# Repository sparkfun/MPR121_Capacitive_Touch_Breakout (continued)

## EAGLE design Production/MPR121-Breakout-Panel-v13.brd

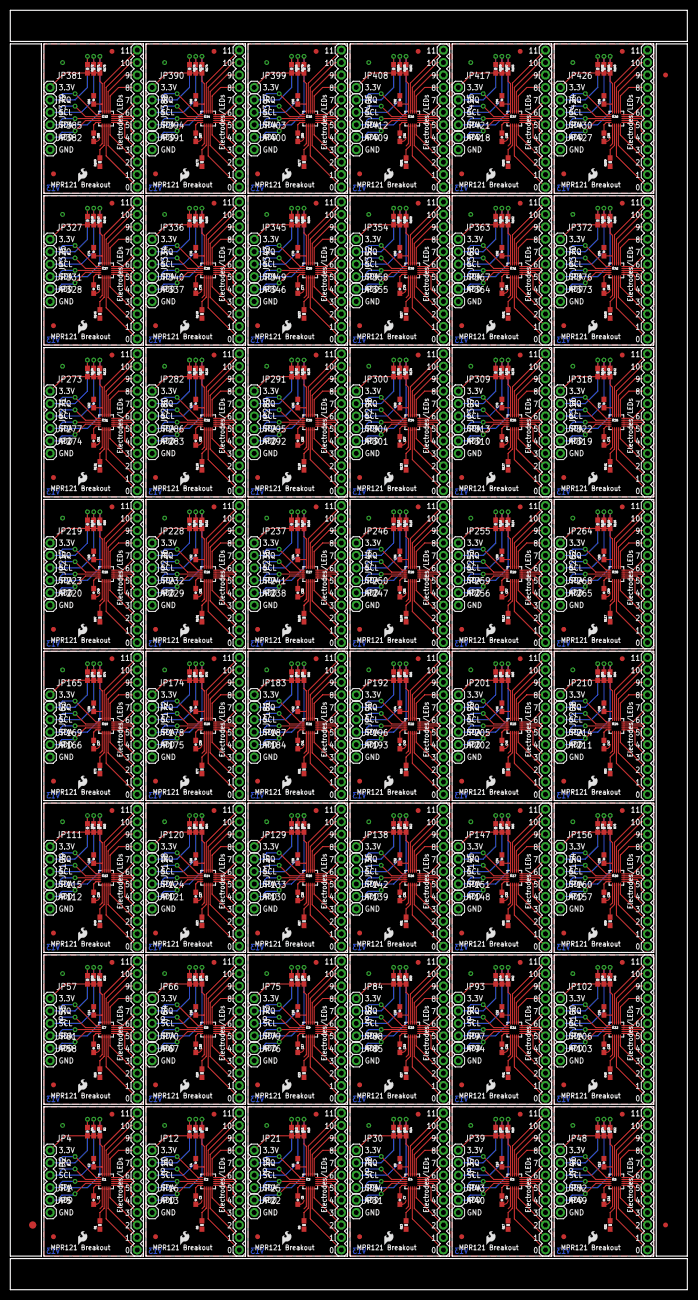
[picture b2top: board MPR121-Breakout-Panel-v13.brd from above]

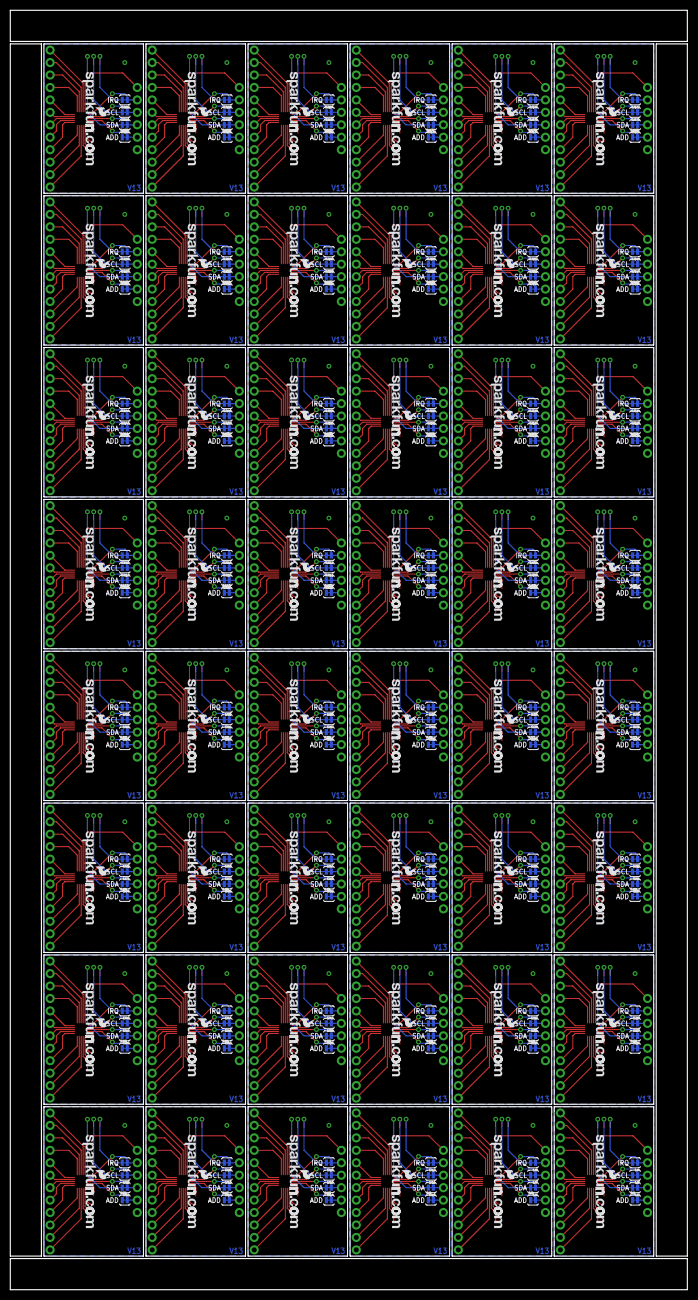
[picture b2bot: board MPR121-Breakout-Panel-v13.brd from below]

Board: 2 copper layers, 138.2 x 261.1 mm, 963 parts (240 on the bottom side), 1104 nets.

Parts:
C1, C2, C3, C4, C5, C6, C7, C8, C9, C10, C11, C12, C13, C14, C15, C16, C17, C18, C19, C20, C21, C22, C23, C24, C25, C26, C27, C28, C29, C30, C31, C32, C33, C34, C35, C36, C37, C38, C39, C40, C41, C42, C43, C44, C45, C46, C47, C48, C49, C50, C51, C52, C53, C54, C55, C56, C57, C58, C59, C60, C61, C62, C63, C64, C65, C66, C67, C68, C69, C70, C71, C72, C73, C74, C75, C76, C77, C78, C79, C80, C81, C82, C83, C84, C85, C86, C87, C88, C89, C90, C91, C92, C93, C94, C95, C96: 0.1uF; 0603-CAP
E$1: FIDUCIAL-1.5X3
E$4, E$5: FIDUCIAL-1X2
IC1, IC2, IC3, IC4, IC5, IC6, IC7, IC8, IC9, IC10, IC11, IC12, IC13, IC14, IC15, IC16, IC17, IC18, IC19, IC20, IC21, IC22, IC23, IC24, IC25, IC26, IC27, IC28, IC29, IC30, IC31, IC32, IC33, IC34, IC35, IC36, IC37, IC38, IC39, IC40, IC41, IC42, IC43, IC44, IC45, IC46, IC47, IC48: MPR121; QFN-20-0.4MM-V2
JP1, JP16, JP25, JP34, JP43, JP52, JP61, JP70, JP79, JP88, JP97, JP106, JP115, JP124, JP133, JP142, JP151, JP160, JP169, JP178, JP187, JP196, JP205, JP214, JP223, JP232, JP241, JP250, JP259, JP268, JP277, JP286, JP295, JP304, JP313, JP322, JP331, JP340, JP349, JP358, JP367, JP376, JP385, JP394, JP403, JP412, JP421, JP430: ADDR; 1X01
JP2, JP10, JP19, JP28, JP37, JP46, JP55, JP64, JP73, JP82, JP91, JP100, JP109, JP118, JP127, JP136, JP145, JP154, JP163, JP172, JP181, JP190, JP199, JP208, JP217, JP226, JP235, JP244, JP253, JP262, JP271, JP280, JP289, JP298, JP307, JP316, JP325, JP334, JP343, JP352, JP361, JP370, JP379, JP388, JP397, JP406, JP415, JP424: I2C; 1X03
JP3, JP11, JP20, JP29, JP38, JP47, JP56, JP65, JP74, JP83, JP92, JP101, JP110, JP119, JP128, JP137, JP146, JP155, JP164, JP173, JP182, JP191, JP200, JP209, JP218, JP227, JP236, JP245, JP254, JP263, JP272, JP281, JP290, JP299, JP308, JP317, JP326, JP335, JP344, JP353, JP362, JP371, JP380, JP389, JP398, JP407, JP416, JP425: Electrodes; 1X12
JP4, JP12, JP21, JP30, JP39, JP48, JP57, JP66, JP75, JP84, JP93, JP102, JP111, JP120, JP129, JP138, JP147, JP156, JP165, JP174, JP183, JP192, JP201, JP210, JP219, JP228, JP237, JP246, JP255, JP264, JP273, JP282, JP291, JP300, JP309, JP318, JP327, JP336, JP345, JP354, JP363, JP372, JP381, JP390, JP399, JP408, JP417, JP426: 3.3V; 1X01
JP5, JP13, JP22, JP31, JP40, JP49, JP58, JP67, JP76, JP85, JP94, JP103, JP112, JP121, JP130, JP139, JP148, JP157, JP166, JP175, JP184, JP193, JP202, JP211, JP220, JP229, JP238, JP247, JP256, JP265, JP274, JP283, JP292, JP301, JP310, JP319, JP328, JP337, JP346, JP355, JP364, JP373, JP382, JP391, JP400, JP409, JP418, JP427: GND; 1X01
JP6, JP14, JP23, JP32, JP41, JP50, JP59, JP68, JP77, JP86, JP95, JP104, JP113, JP122, JP131, JP140, JP149, JP158, JP167, JP176, JP185, JP194, JP203, JP212, JP221, JP230, JP239, JP248, JP257, JP266, JP275, JP284, JP293, JP302, JP311, JP320, JP329, JP338, JP347, JP356, JP365, JP374, JP383, JP392, JP401, JP410, JP419, JP428: LOGO-SFESK; SFE-LOGO-FLAME
JP7, JP15, JP24, JP33, JP42, JP51, JP60, JP69, JP78, JP87, JP96, JP105, JP114, JP123, JP132, JP141, JP150, JP159, JP168, JP177, JP186, JP195, JP204, JP213, JP222, JP231, JP240, JP249, JP258, JP267, JP276, JP285, JP294, JP303, JP312, JP321, JP330, JP339, JP348, JP357, JP366, JP375, JP384, JP393, JP402, JP411, JP420, JP429: LOGO-SFENEW; SFE-NEW-WEBLOGO
JP8, JP9, JP17, JP18, JP26, JP27, JP35, JP36, JP44, JP45, JP53, JP54, JP62, JP63, JP71, JP72, JP80, JP81, JP89, JP90, JP98, JP99, JP107, JP108, JP116, JP117, JP125, JP126, JP134, JP135, JP143, JP144, JP152, JP153, JP161, JP162, JP170, JP171, JP179, JP180, JP188, JP189, JP197, JP198, JP206, JP207, JP215, JP216, JP224, JP225, JP233, JP234, JP242, JP243, JP251, JP252, JP260, JP261, JP269, JP270, JP278, JP279, JP287, JP288, JP296, JP297, JP305, JP306, JP314, JP315, JP323, JP324, JP332, JP333, JP341, JP342, JP350, JP351, JP359, JP360, JP368, JP369, JP377, JP378, JP386, JP387, JP395, JP396, JP404, JP405, JP413, JP414, JP422, JP423, JP431, JP432: FIDUCIAL1X2; FIDUCIAL-1X2
R1, R5, R9, R13, R17, R21, R25, R29, R33, R37, R41, R45, R49, R53, R57, R61, R65, R69, R73, R77, R81, R85, R89, R93, R97, R101, R105, R109, R113, R117, R121, R125, R129, R133, R137, R141, R145, R149, R153, R157, R161, R165, R169, R173, R177, R181, R185, R189: 75k; 0603-RES
R2, R3, R4, R6, R7, R8, R10, R11, R12, R14, R15, R16, R18, R19, R20, R22, R23, R24, R26, R27, R28, R30, R31, R32, R34, R35, R36, R38, R39, R40, R42, R43, R44, R46, R47, R48, R50, R51, R52, R54, R55, R56, R58, R59, R60, R62, R63, R64, R66, R67, R68, R70, R71, R72, R74, R75, R76, R78, R79, R80, R82, R83, R84, R86, R87, R88, R90, R91, R92, R94, R95, R96, R98, R99, R100, R102, R103, R104, R106, R107, R108, R110, R111, R112, R114, R115, R116, R118, R119, R120, R122, R123, R124, R126, R127, R128, R130, R131, R132, R134, R135, R136, R138, R139, R140, R142, R143, R144, R146, R147, R148, R150, R151, R152, R154, R155, R156, R158, R159, R160, R162, R163, R164, R166, R167, R168, R170, R171, R172, R174, R175, R176, R178, R179, R180, R182, R183, R184, R186, R187, R188, R190, R191, R192: 10k; 0603-RES
SJ1, SJ2, SJ3, SJ4, SJ5, SJ6, SJ7, SJ8, SJ9, SJ10, SJ11, SJ12, SJ13, SJ14, SJ15, SJ16, SJ17, SJ18, SJ19, SJ20, SJ21, SJ22, SJ23, SJ24, SJ25, SJ26, SJ27, SJ28, SJ29, SJ30, SJ31, SJ32, SJ33, SJ34, SJ35, SJ36, SJ37, SJ38, SJ39, SJ40, SJ41, SJ42, SJ43, SJ44, SJ45, SJ46, SJ47, SJ48, SJ49, SJ50, SJ51, SJ52, SJ53, SJ54, SJ55, SJ56, SJ57, SJ58, SJ59, SJ60, SJ61, SJ62, SJ63, SJ64, SJ65, SJ66, SJ67, SJ68, SJ69, SJ70, SJ71, SJ72, SJ73, SJ74, SJ75, SJ76, SJ77, SJ78, SJ79, SJ80, SJ81, SJ82, SJ83, SJ84, SJ85, SJ86, SJ87, SJ88, SJ89, SJ90, SJ91, SJ92, SJ93, SJ94, SJ95, SJ96, SJ97, SJ98, SJ99, SJ100, SJ101, SJ102, SJ103, SJ104, SJ105, SJ106, SJ107, SJ108, SJ109, SJ110, SJ111, SJ112, SJ113, SJ114, SJ115, SJ116, SJ117, SJ118, SJ119, SJ120, SJ121, SJ122, SJ123, SJ124, SJ125, SJ126, SJ127, SJ128, SJ129, SJ130, SJ131, SJ132, SJ133, SJ134, SJ135, SJ136, SJ137, SJ138, SJ139, SJ140, SJ141, SJ142, SJ143, SJ144, SJ145, SJ146, SJ147, SJ148, SJ149, SJ150, SJ151, SJ152, SJ153, SJ154, SJ155, SJ156, SJ157, SJ158, SJ159, SJ160, SJ161, SJ162, SJ163, SJ164, SJ165, SJ166, SJ167, SJ168, SJ169, SJ170, SJ171, SJ172, SJ173, SJ174, SJ175, SJ176, SJ177, SJ178, SJ179, SJ180, SJ181, SJ182, SJ183, SJ184, SJ185, SJ186, SJ187, SJ188, SJ189, SJ190, SJ191, SJ192: SOLDERJUMPERTRACE; SJ_2S-TRACE

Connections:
3.3V: C2.1, IC1.20, JP4.1, R2.2, R3.2, R4.2
3.3V1: C4.1, IC2.20, JP12.1, R6.2, R7.2, R8.2
3.3V2: C6.1, IC3.20, JP21.1, R10.2, R11.2, R12.2
3.3V3: C8.1, IC4.20, JP30.1, R14.2, R15.2, R16.2
3.3V4: C10.1, IC5.20, JP39.1, R18.2, R19.2, R20.2
3.3V5: C12.1, IC6.20, JP48.1, R22.2, R23.2, R24.2
3.3V6: C14.1, IC7.20, JP57.1, R26.2, R27.2, R28.2
3.3V7: C16.1, IC8.20, JP66.1, R30.2, R31.2, R32.2
3.3V8: C18.1, IC9.20, JP75.1, R34.2, R35.2, R36.2
3.3V9: C20.1, IC10.20, JP84.1, R38.2, R39.2, R40.2
3.3V10: C22.1, IC11.20, JP93.1, R42.2, R43.2, R44.2
3.3V11: C24.1, IC12.20, JP102.1, R46.2, R47.2, R48.2
3.3V12: C26.1, IC13.20, JP111.1, R50.2, R51.2, R52.2
3.3V13: C28.1, IC14.20, JP120.1, R54.2, R55.2, R56.2
3.3V14: C30.1, IC15.20, JP129.1, R58.2, R59.2, R60.2
3.3V15: C32.1, IC16.20, JP138.1, R62.2, R63.2, R64.2
3.3V16: C34.1, IC17.20, JP147.1, R66.2, R67.2, R68.2
3.3V17: C36.1, IC18.20, JP156.1, R70.2, R71.2, R72.2
3.3V18: C38.1, IC19.20, JP165.1, R74.2, R75.2, R76.2
3.3V19: C40.1, IC20.20, JP174.1, R78.2, R79.2, R80.2
3.3V20: C42.1, IC21.20, JP183.1, R82.2, R83.2, R84.2
3.3V21: C44.1, IC22.20, JP192.1, R86.2, R87.2, R88.2
3.3V22: C46.1, IC23.20, JP201.1, R90.2, R91.2, R92.2
3.3V23: C48.1, IC24.20, JP210.1, R94.2, R95.2, R96.2
3.3V24: C50.1, IC25.20, JP219.1, R98.2, R99.2, R100.2
3.3V25: C52.1, IC26.20, JP228.1, R102.2, R103.2, R104.2
3.3V26: C54.1, IC27.20, JP237.1, R106.2, R107.2, R108.2
3.3V27: C56.1, IC28.20, JP246.1, R110.2, R111.2, R112.2
3.3V28: C58.1, IC29.20, JP255.1, R114.2, R115.2, R116.2
3.3V29: C60.1, IC30.20, JP264.1, R118.2, R119.2, R120.2
3.3V30: C62.1, IC31.20, JP273.1, R122.2, R123.2, R124.2
3.3V31: C64.1, IC32.20, JP282.1, R126.2, R127.2, R128.2
3.3V32: C66.1, IC33.20, JP291.1, R130.2, R131.2, R132.2
3.3V33: C68.1, IC34.20, JP300.1, R134.2, R135.2, R136.2
3.3V34: C70.1, IC35.20, JP309.1, R138.2, R139.2, R140.2
3.3V35: C72.1, IC36.20, JP318.1, R142.2, R143.2, R144.2
3.3V36: C74.1, IC37.20, JP327.1, R146.2, R147.2, R148.2
3.3V37: C76.1, IC38.20, JP336.1, R150.2, R151.2, R152.2
3.3V38: C78.1, IC39.20, JP345.1, R154.2, R155.2, R156.2
3.3V39: C80.1, IC40.20, JP354.1, R158.2, R159.2, R160.2
3.3V40: C82.1, IC41.20, JP363.1, R162.2, R163.2, R164.2
3.3V41: C84.1, IC42.20, JP372.1, R166.2, R167.2, R168.2
3.3V42: C86.1, IC43.20, JP381.1, R170.2, R171.2, R172.2
3.3V43: C88.1, IC44.20, JP390.1, R174.2, R175.2, R176.2
3.3V44: C90.1, IC45.20, JP399.1, R178.2, R179.2, R180.2
3.3V45: C92.1, IC46.20, JP408.1, R182.2, R183.2, R184.2
3.3V46: C94.1, IC47.20, JP417.1, R186.2, R187.2, R188.2
3.3V47: C96.1, IC48.20, JP426.1, R190.2, R191.2, R192.2
ADDR: IC1.4, JP1.1, SJ1.2
ADDR1: IC2.4, JP16.1, SJ5.2
ADDR2: IC3.4, JP25.1, SJ9.2
ADDR3: IC4.4, JP34.1, SJ13.2
ADDR4: IC5.4, JP43.1, SJ17.2
ADDR5: IC6.4, JP52.1, SJ21.2
ADDR6: IC7.4, JP61.1, SJ25.2
ADDR7: IC8.4, JP70.1, SJ29.2
ADDR8: IC9.4, JP79.1, SJ33.2
ADDR9: IC10.4, JP88.1, SJ37.2
ADDR10: IC11.4, JP97.1, SJ41.2
ADDR11: IC12.4, JP106.1, SJ45.2
ADDR12: IC13.4, JP115.1, SJ49.2
ADDR13: IC14.4, JP124.1, SJ53.2
ADDR14: IC15.4, JP133.1, SJ57.2
ADDR15: IC16.4, JP142.1, SJ61.2
ADDR16: IC17.4, JP151.1, SJ65.2
ADDR17: IC18.4, JP160.1, SJ69.2
ADDR18: IC19.4, JP169.1, SJ73.2
ADDR19: IC20.4, JP178.1, SJ77.2
ADDR20: IC21.4, JP187.1, SJ81.2
ADDR21: IC22.4, JP196.1, SJ85.2
ADDR22: IC23.4, JP205.1, SJ89.2
ADDR23: IC24.4, JP214.1, SJ93.2
ADDR24: IC25.4, JP223.1, SJ97.2
ADDR25: IC26.4, JP232.1, SJ101.2
ADDR26: IC27.4, JP241.1, SJ105.2
ADDR27: IC28.4, JP250.1, SJ109.2
ADDR28: IC29.4, JP259.1, SJ113.2
ADDR29: IC30.4, JP268.1, SJ117.2
ADDR30: IC31.4, JP277.1, SJ121.2
ADDR31: IC32.4, JP286.1, SJ125.2
ADDR32: IC33.4, JP295.1, SJ129.2
ADDR33: IC34.4, JP304.1, SJ133.2
ADDR34: IC35.4, JP313.1, SJ137.2
ADDR35: IC36.4, JP322.1, SJ141.2
ADDR36: IC37.4, JP331.1, SJ145.2
ADDR37: IC38.4, JP340.1, SJ149.2
ADDR38: IC39.4, JP349.1, SJ153.2
ADDR39: IC40.4, JP358.1, SJ157.2
ADDR40: IC41.4, JP367.1, SJ161.2
ADDR41: IC42.4, JP376.1, SJ165.2
ADDR42: IC43.4, JP385.1, SJ169.2
ADDR43: IC44.4, JP394.1, SJ173.2
ADDR44: IC45.4, JP403.1, SJ177.2
ADDR45: IC46.4, JP412.1, SJ181.2
ADDR46: IC47.4, JP421.1, SJ185.2
ADDR47: IC48.4, JP430.1, SJ189.2
ELE0: IC1.8, JP3.12
ELE1: IC1.9, JP3.11
ELE2: IC1.10, JP3.10
ELE3: IC1.11, JP3.9
ELE4: IC1.12, JP3.8
ELE5: IC1.13, JP3.7
ELE6: IC1.14, JP3.6
ELE7: IC1.15, JP3.5
ELE8: IC1.16, JP3.4
ELE9: IC1.17, JP3.3
ELE10: IC1.18, JP3.2
ELE11: IC1.19, JP3.1
ELE12: IC2.19, JP11.1
ELE13: IC2.18, JP11.2
ELE14: IC2.17, JP11.3
ELE15: IC2.16, JP11.4
ELE16: IC2.15, JP11.5
ELE17: IC2.14, JP11.6
ELE18: IC2.13, JP11.7
ELE19: IC2.12, JP11.8
ELE20: IC2.11, JP11.9
ELE21: IC2.10, JP11.10
ELE22: IC2.9, JP11.11
ELE23: IC2.8, JP11.12
ELE24: IC3.19, JP20.1
ELE25: IC3.18, JP20.2
ELE26: IC3.17, JP20.3
ELE27: IC3.16, JP20.4
ELE28: IC3.15, JP20.5
ELE29: IC3.14, JP20.6
ELE30: IC3.13, JP20.7
ELE31: IC3.12, JP20.8
ELE32: IC3.11, JP20.9
ELE33: IC3.10, JP20.10
ELE34: IC3.9, JP20.11
ELE35: IC3.8, JP20.12
ELE36: IC4.19, JP29.1
ELE37: IC4.18, JP29.2
ELE38: IC4.17, JP29.3
ELE39: IC4.16, JP29.4
ELE40: IC4.15, JP29.5
ELE41: IC4.14, JP29.6
ELE42: IC4.13, JP29.7
ELE43: IC4.12, JP29.8
ELE44: IC4.11, JP29.9
ELE45: IC4.10, JP29.10
ELE46: IC4.9, JP29.11
ELE47: IC4.8, JP29.12
ELE48: IC5.19, JP38.1
ELE49: IC5.18, JP38.2
ELE50: IC5.17, JP38.3
ELE51: IC5.16, JP38.4
ELE52: IC5.15, JP38.5
ELE53: IC5.14, JP38.6
ELE54: IC5.13, JP38.7
ELE55: IC5.12, JP38.8
ELE56: IC5.11, JP38.9
ELE57: IC5.10, JP38.10
ELE58: IC5.9, JP38.11
ELE59: IC5.8, JP38.12
ELE60: IC6.19, JP47.1
ELE61: IC6.18, JP47.2
ELE62: IC6.17, JP47.3
ELE63: IC6.16, JP47.4
ELE64: IC6.15, JP47.5
ELE65: IC6.14, JP47.6
ELE66: IC6.13, JP47.7
ELE67: IC6.12, JP47.8
ELE68: IC6.11, JP47.9
ELE69: IC6.10, JP47.10
ELE70: IC6.9, JP47.11
ELE71: IC6.8, JP47.12
ELE72: IC7.19, JP56.1
ELE73: IC7.18, JP56.2
ELE74: IC7.17, JP56.3
ELE75: IC7.16, JP56.4
ELE76: IC7.15, JP56.5
ELE77: IC7.14, JP56.6
ELE78: IC7.13, JP56.7
ELE79: IC7.12, JP56.8
ELE80: IC7.11, JP56.9
ELE81: IC7.10, JP56.10
ELE82: IC7.9, JP56.11
ELE83: IC7.8, JP56.12
ELE84: IC8.19, JP65.1
ELE85: IC8.18, JP65.2
ELE86: IC8.17, JP65.3
ELE87: IC8.16, JP65.4
ELE88: IC8.15, JP65.5
ELE89: IC8.14, JP65.6
ELE90: IC8.13, JP65.7
ELE91: IC8.12, JP65.8
ELE92: IC8.11, JP65.9
ELE93: IC8.10, JP65.10
ELE94: IC8.9, JP65.11
ELE95: IC8.8, JP65.12
ELE96: IC9.19, JP74.1
ELE97: IC9.18, JP74.2
ELE98: IC9.17, JP74.3
ELE99: IC9.16, JP74.4
ELE100: IC9.15, JP74.5
ELE101: IC9.14, JP74.6
ELE102: IC9.13, JP74.7
ELE103: IC9.12, JP74.8
ELE104: IC9.11, JP74.9
ELE105: IC9.10, JP74.10
ELE106: IC9.9, JP74.11
ELE107: IC9.8, JP74.12
ELE108: IC10.19, JP83.1
ELE109: IC10.18, JP83.2
ELE110: IC10.17, JP83.3
ELE111: IC10.16, JP83.4
ELE112: IC10.15, JP83.5
ELE113: IC10.14, JP83.6
ELE114: IC10.13, JP83.7
ELE115: IC10.12, JP83.8
ELE116: IC10.11, JP83.9
ELE117: IC10.10, JP83.10
ELE118: IC10.9, JP83.11
ELE119: IC10.8, JP83.12
ELE120: IC11.19, JP92.1
ELE121: IC11.18, JP92.2
ELE122: IC11.17, JP92.3
ELE123: IC11.16, JP92.4
ELE124: IC11.15, JP92.5
ELE125: IC11.14, JP92.6
ELE126: IC11.13, JP92.7
ELE127: IC11.12, JP92.8
ELE128: IC11.11, JP92.9
ELE129: IC11.10, JP92.10
ELE130: IC11.9, JP92.11
ELE131: IC11.8, JP92.12
ELE132: IC12.19, JP101.1
ELE133: IC12.18, JP101.2
ELE134: IC12.17, JP101.3
ELE135: IC12.16, JP101.4
ELE136: IC12.15, JP101.5
ELE137: IC12.14, JP101.6
ELE138: IC12.13, JP101.7
ELE139: IC12.12, JP101.8
ELE140: IC12.11, JP101.9
ELE141: IC12.10, JP101.10
ELE142: IC12.9, JP101.11
ELE143: IC12.8, JP101.12
ELE144: IC13.19, JP110.1
ELE145: IC13.18, JP110.2
ELE146: IC13.17, JP110.3
ELE147: IC13.16, JP110.4
ELE148: IC13.15, JP110.5
ELE149: IC13.14, JP110.6
ELE150: IC13.13, JP110.7
ELE151: IC13.12, JP110.8
ELE152: IC13.11, JP110.9
ELE153: IC13.10, JP110.10
ELE154: IC13.9, JP110.11
ELE155: IC13.8, JP110.12
ELE156: IC14.19, JP119.1
ELE157: IC14.18, JP119.2
ELE158: IC14.17, JP119.3
ELE159: IC14.16, JP119.4
ELE160: IC14.15, JP119.5
ELE161: IC14.14, JP119.6
ELE162: IC14.13, JP119.7
ELE163: IC14.12, JP119.8
ELE164: IC14.11, JP119.9
ELE165: IC14.10, JP119.10
ELE166: IC14.9, JP119.11
ELE167: IC14.8, JP119.12
ELE168: IC15.19, JP128.1
ELE169: IC15.18, JP128.2
ELE170: IC15.17, JP128.3
ELE171: IC15.16, JP128.4
ELE172: IC15.15, JP128.5
ELE173: IC15.14, JP128.6
ELE174: IC15.13, JP128.7
ELE175: IC15.12, JP128.8
ELE176: IC15.11, JP128.9
ELE177: IC15.10, JP128.10
ELE178: IC15.9, JP128.11
ELE179: IC15.8, JP128.12
ELE180: IC16.19, JP137.1
ELE181: IC16.18, JP137.2
ELE182: IC16.17, JP137.3
ELE183: IC16.16, JP137.4
ELE184: IC16.15, JP137.5
ELE185: IC16.14, JP137.6
ELE186: IC16.13, JP137.7
ELE187: IC16.12, JP137.8
ELE188: IC16.11, JP137.9
ELE189: IC16.10, JP137.10
ELE190: IC16.9, JP137.11
ELE191: IC16.8, JP137.12
ELE192: IC17.19, JP146.1
ELE193: IC17.18, JP146.2
ELE194: IC17.17, JP146.3
ELE195: IC17.16, JP146.4
ELE196: IC17.15, JP146.5
ELE197: IC17.14, JP146.6
ELE198: IC17.13, JP146.7
ELE199: IC17.12, JP146.8
ELE200: IC17.11, JP146.9
ELE201: IC17.10, JP146.10
ELE202: IC17.9, JP146.11
ELE203: IC17.8, JP146.12
ELE204: IC18.19, JP155.1
ELE205: IC18.18, JP155.2
ELE206: IC18.17, JP155.3
ELE207: IC18.16, JP155.4
ELE208: IC18.15, JP155.5
ELE209: IC18.14, JP155.6
ELE210: IC18.13, JP155.7
ELE211: IC18.12, JP155.8
ELE212: IC18.11, JP155.9
ELE213: IC18.10, JP155.10
ELE214: IC18.9, JP155.11
ELE215: IC18.8, JP155.12
ELE216: IC19.19, JP164.1
ELE217: IC19.18, JP164.2
ELE218: IC19.17, JP164.3
ELE219: IC19.16, JP164.4
ELE220: IC19.15, JP164.5
ELE221: IC19.14, JP164.6
ELE222: IC19.13, JP164.7
ELE223: IC19.12, JP164.8
ELE224: IC19.11, JP164.9
ELE225: IC19.10, JP164.10
ELE226: IC19.9, JP164.11
ELE227: IC19.8, JP164.12
ELE228: IC20.19, JP173.1
ELE229: IC20.18, JP173.2
ELE230: IC20.17, JP173.3
ELE231: IC20.16, JP173.4
ELE232: IC20.15, JP173.5
ELE233: IC20.14, JP173.6
ELE234: IC20.13, JP173.7
ELE235: IC20.12, JP173.8
ELE236: IC20.11, JP173.9
ELE237: IC20.10, JP173.10
ELE238: IC20.9, JP173.11
ELE239: IC20.8, JP173.12
ELE240: IC21.19, JP182.1
ELE241: IC21.18, JP182.2
ELE242: IC21.17, JP182.3
ELE243: IC21.16, JP182.4
ELE244: IC21.15, JP182.5
ELE245: IC21.14, JP182.6
ELE246: IC21.13, JP182.7
ELE247: IC21.12, JP182.8
ELE248: IC21.11, JP182.9
ELE249: IC21.10, JP182.10
ELE250: IC21.9, JP182.11
ELE251: IC21.8, JP182.12
ELE252: IC22.19, JP191.1
ELE253: IC22.18, JP191.2
ELE254: IC22.17, JP191.3
ELE255: IC22.16, JP191.4
ELE256: IC22.15, JP191.5
ELE257: IC22.14, JP191.6
ELE258: IC22.13, JP191.7
ELE259: IC22.12, JP191.8
ELE260: IC22.11, JP191.9
ELE261: IC22.10, JP191.10
ELE262: IC22.9, JP191.11
ELE263: IC22.8, JP191.12
ELE264: IC23.19, JP200.1
ELE265: IC23.18, JP200.2
ELE266: IC23.17, JP200.3
ELE267: IC23.16, JP200.4
ELE268: IC23.15, JP200.5
ELE269: IC23.14, JP200.6
ELE270: IC23.13, JP200.7
ELE271: IC23.12, JP200.8
ELE272: IC23.11, JP200.9
ELE273: IC23.10, JP200.10
ELE274: IC23.9, JP200.11
ELE275: IC23.8, JP200.12
ELE276: IC24.19, JP209.1
ELE277: IC24.18, JP209.2
ELE278: IC24.17, JP209.3
ELE279: IC24.16, JP209.4
ELE280: IC24.15, JP209.5
ELE281: IC24.14, JP209.6
ELE282: IC24.13, JP209.7
ELE283: IC24.12, JP209.8
ELE284: IC24.11, JP209.9
ELE285: IC24.10, JP209.10
ELE286: IC24.9, JP209.11
ELE287: IC24.8, JP209.12
ELE288: IC25.19, JP218.1
ELE289: IC25.18, JP218.2
ELE290: IC25.17, JP218.3
ELE291: IC25.16, JP218.4
ELE292: IC25.15, JP218.5
ELE293: IC25.14, JP218.6
ELE294: IC25.13, JP218.7
ELE295: IC25.12, JP218.8
ELE296: IC25.11, JP218.9
ELE297: IC25.10, JP218.10
ELE298: IC25.9, JP218.11
ELE299: IC25.8, JP218.12
ELE300: IC26.19, JP227.1
ELE301: IC26.18, JP227.2
ELE302: IC26.17, JP227.3
ELE303: IC26.16, JP227.4
ELE304: IC26.15, JP227.5
ELE305: IC26.14, JP227.6
ELE306: IC26.13, JP227.7
ELE307: IC26.12, JP227.8
ELE308: IC26.11, JP227.9
ELE309: IC26.10, JP227.10
ELE310: IC26.9, JP227.11
ELE311: IC26.8, JP227.12
ELE312: IC27.19, JP236.1
ELE313: IC27.18, JP236.2
ELE314: IC27.17, JP236.3
ELE315: IC27.16, JP236.4
ELE316: IC27.15, JP236.5
ELE317: IC27.14, JP236.6
ELE318: IC27.13, JP236.7
ELE319: IC27.12, JP236.8
ELE320: IC27.11, JP236.9
ELE321: IC27.10, JP236.10
ELE322: IC27.9, JP236.11
ELE323: IC27.8, JP236.12
ELE324: IC28.19, JP245.1
ELE325: IC28.18, JP245.2
ELE326: IC28.17, JP245.3
ELE327: IC28.16, JP245.4
ELE328: IC28.15, JP245.5
ELE329: IC28.14, JP245.6
ELE330: IC28.13, JP245.7
ELE331: IC28.12, JP245.8
ELE332: IC28.11, JP245.9
ELE333: IC28.10, JP245.10
ELE334: IC28.9, JP245.11
ELE335: IC28.8, JP245.12
ELE336: IC29.19, JP254.1
ELE337: IC29.18, JP254.2
ELE338: IC29.17, JP254.3
ELE339: IC29.16, JP254.4
ELE340: IC29.15, JP254.5
ELE341: IC29.14, JP254.6
ELE342: IC29.13, JP254.7
ELE343: IC29.12, JP254.8
ELE344: IC29.11, JP254.9
ELE345: IC29.10, JP254.10
ELE346: IC29.9, JP254.11
ELE347: IC29.8, JP254.12
ELE348: IC30.19, JP263.1
ELE349: IC30.18, JP263.2
ELE350: IC30.17, JP263.3
ELE351: IC30.16, JP263.4
ELE352: IC30.15, JP263.5
ELE353: IC30.14, JP263.6
ELE354: IC30.13, JP263.7
ELE355: IC30.12, JP263.8
ELE356: IC30.11, JP263.9
ELE357: IC30.10, JP263.10
ELE358: IC30.9, JP263.11
ELE359: IC30.8, JP263.12
ELE360: IC31.19, JP272.1
ELE361: IC31.18, JP272.2
ELE362: IC31.17, JP272.3
ELE363: IC31.16, JP272.4
ELE364: IC31.15, JP272.5
ELE365: IC31.14, JP272.6
ELE366: IC31.13, JP272.7
ELE367: IC31.12, JP272.8
ELE368: IC31.11, JP272.9
ELE369: IC31.10, JP272.10
ELE370: IC31.9, JP272.11
ELE371: IC31.8, JP272.12
ELE372: IC32.19, JP281.1
ELE373: IC32.18, JP281.2
ELE374: IC32.17, JP281.3
ELE375: IC32.16, JP281.4
ELE376: IC32.15, JP281.5
ELE377: IC32.14, JP281.6
ELE378: IC32.13, JP281.7
ELE379: IC32.12, JP281.8
ELE380: IC32.11, JP281.9
ELE381: IC32.10, JP281.10
ELE382: IC32.9, JP281.11
ELE383: IC32.8, JP281.12
ELE384: IC33.19, JP290.1
ELE385: IC33.18, JP290.2
ELE386: IC33.17, JP290.3
ELE387: IC33.16, JP290.4
ELE388: IC33.15, JP290.5
ELE389: IC33.14, JP290.6
ELE390: IC33.13, JP290.7
ELE391: IC33.12, JP290.8
ELE392: IC33.11, JP290.9
ELE393: IC33.10, JP290.10
ELE394: IC33.9, JP290.11
ELE395: IC33.8, JP290.12
ELE396: IC34.19, JP299.1
ELE397: IC34.18, JP299.2
ELE398: IC34.17, JP299.3
ELE399: IC34.16, JP299.4
ELE400: IC34.15, JP299.5
ELE401: IC34.14, JP299.6
ELE402: IC34.13, JP299.7
ELE403: IC34.12, JP299.8
ELE404: IC34.11, JP299.9
ELE405: IC34.10, JP299.10
ELE406: IC34.9, JP299.11
ELE407: IC34.8, JP299.12
ELE408: IC35.19, JP308.1
ELE409: IC35.18, JP308.2
ELE410: IC35.17, JP308.3
ELE411: IC35.16, JP308.4
ELE412: IC35.15, JP308.5
ELE413: IC35.14, JP308.6
ELE414: IC35.13, JP308.7
ELE415: IC35.12, JP308.8
ELE416: IC35.11, JP308.9
ELE417: IC35.10, JP308.10
ELE418: IC35.9, JP308.11
ELE419: IC35.8, JP308.12
ELE420: IC36.19, JP317.1
ELE421: IC36.18, JP317.2
ELE422: IC36.17, JP317.3
ELE423: IC36.16, JP317.4
ELE424: IC36.15, JP317.5
ELE425: IC36.14, JP317.6
ELE426: IC36.13, JP317.7
ELE427: IC36.12, JP317.8
ELE428: IC36.11, JP317.9
ELE429: IC36.10, JP317.10
ELE430: IC36.9, JP317.11
ELE431: IC36.8, JP317.12
ELE432: IC37.19, JP326.1
ELE433: IC37.18, JP326.2
ELE434: IC37.17, JP326.3
ELE435: IC37.16, JP326.4
ELE436: IC37.15, JP326.5
ELE437: IC37.14, JP326.6
ELE438: IC37.13, JP326.7
ELE439: IC37.12, JP326.8
ELE440: IC37.11, JP326.9
ELE441: IC37.10, JP326.10
ELE442: IC37.9, JP326.11
ELE443: IC37.8, JP326.12
ELE444: IC38.19, JP335.1
ELE445: IC38.18, JP335.2
ELE446: IC38.17, JP335.3
ELE447: IC38.16, JP335.4
ELE448: IC38.15, JP335.5
ELE449: IC38.14, JP335.6
ELE450: IC38.13, JP335.7
ELE451: IC38.12, JP335.8
ELE452: IC38.11, JP335.9
ELE453: IC38.10, JP335.10
ELE454: IC38.9, JP335.11
ELE455: IC38.8, JP335.12
ELE456: IC39.19, JP344.1
ELE457: IC39.18, JP344.2
ELE458: IC39.17, JP344.3
ELE459: IC39.16, JP344.4
ELE460: IC39.15, JP344.5
ELE461: IC39.14, JP344.6
ELE462: IC39.13, JP344.7
ELE463: IC39.12, JP344.8
ELE464: IC39.11, JP344.9
ELE465: IC39.10, JP344.10
ELE466: IC39.9, JP344.11
ELE467: IC39.8, JP344.12
ELE468: IC40.19, JP353.1
ELE469: IC40.18, JP353.2
ELE470: IC40.17, JP353.3
ELE471: IC40.16, JP353.4
ELE472: IC40.15, JP353.5
ELE473: IC40.14, JP353.6
ELE474: IC40.13, JP353.7
ELE475: IC40.12, JP353.8
ELE476: IC40.11, JP353.9
ELE477: IC40.10, JP353.10
ELE478: IC40.9, JP353.11
ELE479: IC40.8, JP353.12
ELE480: IC41.19, JP362.1
ELE481: IC41.18, JP362.2
ELE482: IC41.17, JP362.3
ELE483: IC41.16, JP362.4
ELE484: IC41.15, JP362.5
ELE485: IC41.14, JP362.6
ELE486: IC41.13, JP362.7
ELE487: IC41.12, JP362.8
ELE488: IC41.11, JP362.9
ELE489: IC41.10, JP362.10
ELE490: IC41.9, JP362.11
ELE491: IC41.8, JP362.12
ELE492: IC42.19, JP371.1
ELE493: IC42.18, JP371.2
ELE494: IC42.17, JP371.3
ELE495: IC42.16, JP371.4
ELE496: IC42.15, JP371.5
ELE497: IC42.14, JP371.6
ELE498: IC42.13, JP371.7
ELE499: IC42.12, JP371.8
ELE500: IC42.11, JP371.9
ELE501: IC42.10, JP371.10
ELE502: IC42.9, JP371.11
ELE503: IC42.8, JP371.12
ELE504: IC43.19, JP380.1
ELE505: IC43.18, JP380.2
ELE506: IC43.17, JP380.3
ELE507: IC43.16, JP380.4
ELE508: IC43.15, JP380.5
ELE509: IC43.14, JP380.6
ELE510: IC43.13, JP380.7
ELE511: IC43.12, JP380.8
ELE512: IC43.11, JP380.9
ELE513: IC43.10, JP380.10
ELE514: IC43.9, JP380.11
ELE515: IC43.8, JP380.12
ELE516: IC44.19, JP389.1
ELE517: IC44.18, JP389.2
ELE518: IC44.17, JP389.3
ELE519: IC44.16, JP389.4
ELE520: IC44.15, JP389.5
ELE521: IC44.14, JP389.6
ELE522: IC44.13, JP389.7
ELE523: IC44.12, JP389.8
ELE524: IC44.11, JP389.9
ELE525: IC44.10, JP389.10
ELE526: IC44.9, JP389.11
ELE527: IC44.8, JP389.12
ELE528: IC45.19, JP398.1
ELE529: IC45.18, JP398.2
ELE530: IC45.17, JP398.3
ELE531: IC45.16, JP398.4
ELE532: IC45.15, JP398.5
ELE533: IC45.14, JP398.6
ELE534: IC45.13, JP398.7
ELE535: IC45.12, JP398.8
ELE536: IC45.11, JP398.9
ELE537: IC45.10, JP398.10
ELE538: IC45.9, JP398.11
ELE539: IC45.8, JP398.12
ELE540: IC46.19, JP407.1
ELE541: IC46.18, JP407.2
ELE542: IC46.17, JP407.3
ELE543: IC46.16, JP407.4
ELE544: IC46.15, JP407.5
ELE545: IC46.14, JP407.6
ELE546: IC46.13, JP407.7
ELE547: IC46.12, JP407.8
ELE548: IC46.11, JP407.9
ELE549: IC46.10, JP407.10
ELE550: IC46.9, JP407.11
ELE551: IC46.8, JP407.12
ELE552: IC47.19, JP416.1
ELE553: IC47.18, JP416.2
ELE554: IC47.17, JP416.3
ELE555: IC47.16, JP416.4
ELE556: IC47.15, JP416.5
ELE557: IC47.14, JP416.6
ELE558: IC47.13, JP416.7
ELE559: IC47.12, JP416.8
ELE560: IC47.11, JP416.9
ELE561: IC47.10, JP416.10
ELE562: IC47.9, JP416.11
ELE563: IC47.8, JP416.12
ELE564: IC48.19, JP425.1
ELE565: IC48.18, JP425.2
ELE566: IC48.17, JP425.3
ELE567: IC48.16, JP425.4
ELE568: IC48.15, JP425.5
ELE569: IC48.14, JP425.6
ELE570: IC48.13, JP425.7
ELE571: IC48.12, JP425.8
ELE572: IC48.11, JP425.9
ELE573: IC48.10, JP425.10
ELE574: IC48.9, JP425.11
ELE575: IC48.8, JP425.12
GND: C1.2, C2.2, IC1.6, JP5.1, R1.1, SJ1.1
GND1: C3.2, C4.2, IC2.6, JP13.1, R5.1, SJ5.1
GND2: C5.2, C6.2, IC3.6, JP22.1, R9.1, SJ9.1
GND3: C7.2, C8.2, IC4.6, JP31.1, R13.1, SJ13.1
GND4: C9.2, C10.2, IC5.6, JP40.1, R17.1, SJ17.1
GND5: C11.2, C12.2, IC6.6, JP49.1, R21.1, SJ21.1
GND6: C13.2, C14.2, IC7.6, JP58.1, R25.1, SJ25.1
GND7: C15.2, C16.2, IC8.6, JP67.1, R29.1, SJ29.1
GND8: C17.2, C18.2, IC9.6, JP76.1, R33.1, SJ33.1
GND9: C19.2, C20.2, IC10.6, JP85.1, R37.1, SJ37.1
GND10: C21.2, C22.2, IC11.6, JP94.1, R41.1, SJ41.1
GND11: C23.2, C24.2, IC12.6, JP103.1, R45.1, SJ45.1
GND12: C25.2, C26.2, IC13.6, JP112.1, R49.1, SJ49.1
GND13: C27.2, C28.2, IC14.6, JP121.1, R53.1, SJ53.1
GND14: C29.2, C30.2, IC15.6, JP130.1, R57.1, SJ57.1
GND15: C31.2, C32.2, IC16.6, JP139.1, R61.1, SJ61.1
GND16: C33.2, C34.2, IC17.6, JP148.1, R65.1, SJ65.1
GND17: C35.2, C36.2, IC18.6, JP157.1, R69.1, SJ69.1
GND18: C37.2, C38.2, IC19.6, JP166.1, R73.1, SJ73.1
GND19: C39.2, C40.2, IC20.6, JP175.1, R77.1, SJ77.1
GND20: C41.2, C42.2, IC21.6, JP184.1, R81.1, SJ81.1
GND21: C43.2, C44.2, IC22.6, JP193.1, R85.1, SJ85.1
GND22: C45.2, C46.2, IC23.6, JP202.1, R89.1, SJ89.1
GND23: C47.2, C48.2, IC24.6, JP211.1, R93.1, SJ93.1
GND24: C49.2, C50.2, IC25.6, JP220.1, R97.1, SJ97.1
GND25: C51.2, C52.2, IC26.6, JP229.1, R101.1, SJ101.1
GND26: C53.2, C54.2, IC27.6, JP238.1, R105.1, SJ105.1
GND27: C55.2, C56.2, IC28.6, JP247.1, R109.1, SJ109.1
GND28: C57.2, C58.2, IC29.6, JP256.1, R113.1, SJ113.1
GND29: C59.2, C60.2, IC30.6, JP265.1, R117.1, SJ117.1
GND30: C61.2, C62.2, IC31.6, JP274.1, R121.1, SJ121.1
GND31: C63.2, C64.2, IC32.6, JP283.1, R125.1, SJ125.1
GND32: C65.2, C66.2, IC33.6, JP292.1, R129.1, SJ129.1
GND33: C67.2, C68.2, IC34.6, JP301.1, R133.1, SJ133.1
GND34: C69.2, C70.2, IC35.6, JP310.1, R137.1, SJ137.1
GND35: C71.2, C72.2, IC36.6, JP319.1, R141.1, SJ141.1
GND36: C73.2, C74.2, IC37.6, JP328.1, R145.1, SJ145.1
GND37: C75.2, C76.2, IC38.6, JP337.1, R149.1, SJ149.1
GND38: C77.2, C78.2, IC39.6, JP346.1, R153.1, SJ153.1
GND39: C79.2, C80.2, IC40.6, JP355.1, R157.1, SJ157.1
GND40: C81.2, C82.2, IC41.6, JP364.1, R161.1, SJ161.1
GND41: C83.2, C84.2, IC42.6, JP373.1, R165.1, SJ165.1
GND42: C85.2, C86.2, IC43.6, JP382.1, R169.1, SJ169.1
GND43: C87.2, C88.2, IC44.6, JP391.1, R173.1, SJ173.1
GND44: C89.2, C90.2, IC45.6, JP400.1, R177.1, SJ177.1
GND45: C91.2, C92.2, IC46.6, JP409.1, R181.1, SJ181.1
GND46: C93.2, C94.2, IC47.6, JP418.1, R185.1, SJ185.1
GND47: C95.2, C96.2, IC48.6, JP427.1, R189.1, SJ189.1
REXT: IC1.7, R1.2
REXT1: IC2.7, R5.2
REXT2: IC3.7, R9.2
REXT3: IC4.7, R13.2
REXT4: IC5.7, R17.2
REXT5: IC6.7, R21.2
REXT6: IC7.7, R25.2
REXT7: IC8.7, R29.2
REXT8: IC9.7, R33.2
REXT9: IC10.7, R37.2
REXT10: IC11.7, R41.2
REXT11: IC12.7, R45.2
REXT12: IC13.7, R49.2
REXT13: IC14.7, R53.2
REXT14: IC15.7, R57.2
REXT15: IC16.7, R61.2
REXT16: IC17.7, R65.2
REXT17: IC18.7, R69.2
REXT18: IC19.7, R73.2
REXT19: IC20.7, R77.2
REXT20: IC21.7, R81.2
REXT21: IC22.7, R85.2
REXT22: IC23.7, R89.2
REXT23: IC24.7, R93.2
REXT24: IC25.7, R97.2
REXT25: IC26.7, R101.2
REXT26: IC27.7, R105.2
REXT27: IC28.7, R109.2
REXT28: IC29.7, R113.2
REXT29: IC30.7, R117.2
REXT30: IC31.7, R121.2
REXT31: IC32.7, R125.2
REXT32: IC33.7, R129.2
REXT33: IC34.7, R133.2
REXT34: IC35.7, R137.2
REXT35: IC36.7, R141.2
REXT36: IC37.7, R145.2
REXT37: IC38.7, R149.2
REXT38: IC39.7, R153.2
REXT39: IC40.7, R157.2
REXT40: IC41.7, R161.2
REXT41: IC42.7, R165.2
REXT42: IC43.7, R169.2
REXT43: IC44.7, R173.2
REXT44: IC45.7, R177.2
REXT45: IC46.7, R181.2
REXT46: IC47.7, R185.2
REXT47: IC48.7, R189.2
SCL: IC1.2, JP2.2, SJ3.1
SCL1: IC2.2, JP10.2, SJ7.1
SCL2: IC3.2, JP19.2, SJ11.1
SCL3: IC4.2, JP28.2, SJ15.1
SCL4: IC5.2, JP37.2, SJ19.1
SCL5: IC6.2, JP46.2, SJ23.1
SCL6: IC7.2, JP55.2, SJ27.1
SCL7: IC8.2, JP64.2, SJ31.1
SCL8: IC9.2, JP73.2, SJ35.1
SCL9: IC10.2, JP82.2, SJ39.1
SCL10: IC11.2, JP91.2, SJ43.1
SCL11: IC12.2, JP100.2, SJ47.1
SCL12: IC13.2, JP109.2, SJ51.1
SCL13: IC14.2, JP118.2, SJ55.1
SCL14: IC15.2, JP127.2, SJ59.1
SCL15: IC16.2, JP136.2, SJ63.1
SCL16: IC17.2, JP145.2, SJ67.1
SCL17: IC18.2, JP154.2, SJ71.1
SCL18: IC19.2, JP163.2, SJ75.1
SCL19: IC20.2, JP172.2, SJ79.1
SCL20: IC21.2, JP181.2, SJ83.1
SCL21: IC22.2, JP190.2, SJ87.1
SCL22: IC23.2, JP199.2, SJ91.1
SCL23: IC24.2, JP208.2, SJ95.1
SCL24: IC25.2, JP217.2, SJ99.1
SCL25: IC26.2, JP226.2, SJ103.1
SCL26: IC27.2, JP235.2, SJ107.1
SCL27: IC28.2, JP244.2, SJ111.1
SCL28: IC29.2, JP253.2, SJ115.1
SCL29: IC30.2, JP262.2, SJ119.1
SCL30: IC31.2, JP271.2, SJ123.1
SCL31: IC32.2, JP280.2, SJ127.1
SCL32: IC33.2, JP289.2, SJ131.1
SCL33: IC34.2, JP298.2, SJ135.1
SCL34: IC35.2, JP307.2, SJ139.1
SCL35: IC36.2, JP316.2, SJ143.1
SCL36: IC37.2, JP325.2, SJ147.1
SCL37: IC38.2, JP334.2, SJ151.1
SCL38: IC39.2, JP343.2, SJ155.1
SCL39: IC40.2, JP352.2, SJ159.1
SCL40: IC41.2, JP361.2, SJ163.1
SCL41: IC42.2, JP370.2, SJ167.1
SCL42: IC43.2, JP379.2, SJ171.1
SCL43: IC44.2, JP388.2, SJ175.1
SCL44: IC45.2, JP397.2, SJ179.1
SCL45: IC46.2, JP406.2, SJ183.1
SCL46: IC47.2, JP415.2, SJ187.1
SCL47: IC48.2, JP424.2, SJ191.1
SCL_PU: R3.1, SJ3.2
SCL_PU1: R7.1, SJ7.2
SCL_PU2: R11.1, SJ11.2
SCL_PU3: R15.1, SJ15.2
SCL_PU4: R19.1, SJ19.2
SCL_PU5: R23.1, SJ23.2
SCL_PU6: R27.1, SJ27.2
SCL_PU7: R31.1, SJ31.2
SCL_PU8: R35.1, SJ35.2
SCL_PU9: R39.1, SJ39.2
SCL_PU10: R43.1, SJ43.2
SCL_PU11: R47.1, SJ47.2
SCL_PU12: R51.1, SJ51.2
SCL_PU13: R55.1, SJ55.2
SCL_PU14: R59.1, SJ59.2
SCL_PU15: R63.1, SJ63.2
SCL_PU16: R67.1, SJ67.2
SCL_PU17: R71.1, SJ71.2
SCL_PU18: R75.1, SJ75.2
SCL_PU19: R79.1, SJ79.2
SCL_PU20: R83.1, SJ83.2
SCL_PU21: R87.1, SJ87.2
SCL_PU22: R91.1, SJ91.2
SCL_PU23: R95.1, SJ95.2
SCL_PU24: R99.1, SJ99.2
SCL_PU25: R103.1, SJ103.2
SCL_PU26: R107.1, SJ107.2
SCL_PU27: R111.1, SJ111.2
SCL_PU28: R115.1, SJ115.2
SCL_PU29: R119.1, SJ119.2
SCL_PU30: R123.1, SJ123.2
SCL_PU31: R127.1, SJ127.2
SCL_PU32: R131.1, SJ131.2
SCL_PU33: R135.1, SJ135.2
SCL_PU34: R139.1, SJ139.2
SCL_PU35: R143.1, SJ143.2
SCL_PU36: R147.1, SJ147.2
SCL_PU37: R151.1, SJ151.2
SCL_PU38: R155.1, SJ155.2
SCL_PU39: R159.1, SJ159.2
SCL_PU40: R163.1, SJ163.2
SCL_PU41: R167.1, SJ167.2
SCL_PU42: R171.1, SJ171.2
SCL_PU43: R175.1, SJ175.2
SCL_PU44: R179.1, SJ179.2
SCL_PU45: R183.1, SJ183.2
SCL_PU46: R187.1, SJ187.2
SCL_PU47: R191.1, SJ191.2
SDA: IC1.3, JP2.3, SJ2.1
SDA1: IC2.3, JP10.3, SJ6.1
SDA2: IC3.3, JP19.3, SJ10.1
SDA3: IC4.3, JP28.3, SJ14.1
SDA4: IC5.3, JP37.3, SJ18.1
SDA5: IC6.3, JP46.3, SJ22.1
SDA6: IC7.3, JP55.3, SJ26.1
SDA7: IC8.3, JP64.3, SJ30.1
SDA8: IC9.3, JP73.3, SJ34.1
SDA9: IC10.3, JP82.3, SJ38.1
SDA10: IC11.3, JP91.3, SJ42.1
SDA11: IC12.3, JP100.3, SJ46.1
SDA12: IC13.3, JP109.3, SJ50.1
SDA13: IC14.3, JP118.3, SJ54.1
SDA14: IC15.3, JP127.3, SJ58.1
SDA15: IC16.3, JP136.3, SJ62.1
SDA16: IC17.3, JP145.3, SJ66.1
SDA17: IC18.3, JP154.3, SJ70.1
SDA18: IC19.3, JP163.3, SJ74.1
SDA19: IC20.3, JP172.3, SJ78.1
SDA20: IC21.3, JP181.3, SJ82.1
SDA21: IC22.3, JP190.3, SJ86.1
SDA22: IC23.3, JP199.3, SJ90.1
SDA23: IC24.3, JP208.3, SJ94.1
SDA24: IC25.3, JP217.3, SJ98.1
SDA25: IC26.3, JP226.3, SJ102.1
SDA26: IC27.3, JP235.3, SJ106.1
SDA27: IC28.3, JP244.3, SJ110.1
SDA28: IC29.3, JP253.3, SJ114.1
SDA29: IC30.3, JP262.3, SJ118.1
SDA30: IC31.3, JP271.3, SJ122.1
SDA31: IC32.3, JP280.3, SJ126.1
SDA32: IC33.3, JP289.3, SJ130.1
SDA33: IC34.3, JP298.3, SJ134.1
SDA34: IC35.3, JP307.3, SJ138.1
SDA35: IC36.3, JP316.3, SJ142.1
SDA36: IC37.3, JP325.3, SJ146.1
SDA37: IC38.3, JP334.3, SJ150.1
SDA38: IC39.3, JP343.3, SJ154.1
SDA39: IC40.3, JP352.3, SJ158.1
SDA40: IC41.3, JP361.3, SJ162.1
SDA41: IC42.3, JP370.3, SJ166.1
SDA42: IC43.3, JP379.3, SJ170.1
SDA43: IC44.3, JP388.3, SJ174.1
SDA44: IC45.3, JP397.3, SJ178.1
SDA45: IC46.3, JP406.3, SJ182.1
SDA46: IC47.3, JP415.3, SJ186.1
SDA47: IC48.3, JP424.3, SJ190.1
SDA_PU: R2.1, SJ2.2
SDA_PU1: R6.1, SJ6.2
SDA_PU2: R10.1, SJ10.2
SDA_PU3: R14.1, SJ14.2
SDA_PU4: R18.1, SJ18.2
SDA_PU5: R22.1, SJ22.2
SDA_PU6: R26.1, SJ26.2
SDA_PU7: R30.1, SJ30.2
SDA_PU8: R34.1, SJ34.2
SDA_PU9: R38.1, SJ38.2
SDA_PU10: R42.1, SJ42.2
SDA_PU11: R46.1, SJ46.2
SDA_PU12: R50.1, SJ50.2
SDA_PU13: R54.1, SJ54.2
SDA_PU14: R58.1, SJ58.2
SDA_PU15: R62.1, SJ62.2
SDA_PU16: R66.1, SJ66.2
SDA_PU17: R70.1, SJ70.2
SDA_PU18: R74.1, SJ74.2
SDA_PU19: R78.1, SJ78.2
SDA_PU20: R82.1, SJ82.2
SDA_PU21: R86.1, SJ86.2
SDA_PU22: R90.1, SJ90.2
SDA_PU23: R94.1, SJ94.2
SDA_PU24: R98.1, SJ98.2
SDA_PU25: R102.1, SJ102.2
SDA_PU26: R106.1, SJ106.2
SDA_PU27: R110.1, SJ110.2
SDA_PU28: R114.1, SJ114.2
SDA_PU29: R118.1, SJ118.2
SDA_PU30: R122.1, SJ122.2
SDA_PU31: R126.1, SJ126.2
SDA_PU32: R130.1, SJ130.2
SDA_PU33: R134.1, SJ134.2
SDA_PU34: R138.1, SJ138.2
SDA_PU35: R142.1, SJ142.2
SDA_PU36: R146.1, SJ146.2
SDA_PU37: R150.1, SJ150.2
SDA_PU38: R154.1, SJ154.2
SDA_PU39: R158.1, SJ158.2
SDA_PU40: R162.1, SJ162.2
SDA_PU41: R166.1, SJ166.2
SDA_PU42: R170.1, SJ170.2
SDA_PU43: R174.1, SJ174.2
SDA_PU44: R178.1, SJ178.2
SDA_PU45: R182.1, SJ182.2
SDA_PU46: R186.1, SJ186.2
SDA_PU47: R190.1, SJ190.2
VREG: C1.1, IC1.5
VREG1: C3.1, IC2.5
VREG2: C5.1, IC3.5
VREG3: C7.1, IC4.5
VREG4: C9.1, IC5.5
VREG5: C11.1, IC6.5
VREG6: C13.1, IC7.5
VREG7: C15.1, IC8.5
VREG8: C17.1, IC9.5
VREG9: C19.1, IC10.5
VREG10: C21.1, IC11.5
VREG11: C23.1, IC12.5
VREG12: C25.1, IC13.5
VREG13: C27.1, IC14.5
VREG14: C29.1, IC15.5
VREG15: C31.1, IC16.5
VREG16: C33.1, IC17.5
VREG17: C35.1, IC18.5
VREG18: C37.1, IC19.5
VREG19: C39.1, IC20.5
VREG20: C41.1, IC21.5
VREG21: C43.1, IC22.5
VREG22: C45.1, IC23.5
VREG23: C47.1, IC24.5
VREG24: C49.1, IC25.5
VREG25: C51.1, IC26.5
VREG26: C53.1, IC27.5
VREG27: C55.1, IC28.5
VREG28: C57.1, IC29.5
VREG29: C59.1, IC30.5
VREG30: C61.1, IC31.5
VREG31: C63.1, IC32.5
VREG32: C65.1, IC33.5
VREG33: C67.1, IC34.5
VREG34: C69.1, IC35.5
VREG35: C71.1, IC36.5
VREG36: C73.1, IC37.5
VREG37: C75.1, IC38.5
VREG38: C77.1, IC39.5
VREG39: C79.1, IC40.5
VREG40: C81.1, IC41.5
VREG41: C83.1, IC42.5
VREG42: C85.1, IC43.5
VREG43: C87.1, IC44.5
VREG44: C89.1, IC45.5
VREG45: C91.1, IC46.5
VREG46: C93.1, IC47.5
VREG47: C95.1, IC48.5
~IRQ: IC1.1, JP2.1, SJ4.1
~IRQ1: IC2.1, JP10.1, SJ8.1
~IRQ2: IC3.1, JP19.1, SJ12.1
~IRQ3: IC4.1, JP28.1, SJ16.1
~IRQ4: IC5.1, JP37.1, SJ20.1
~IRQ5: IC6.1, JP46.1, SJ24.1
~IRQ6: IC7.1, JP55.1, SJ28.1
~IRQ7: IC8.1, JP64.1, SJ32.1
~IRQ8: IC9.1, JP73.1, SJ36.1
~IRQ9: IC10.1, JP82.1, SJ40.1
~IRQ10: IC11.1, JP91.1, SJ44.1
~IRQ11: IC12.1, JP100.1, SJ48.1
~IRQ12: IC13.1, JP109.1, SJ52.1
~IRQ13: IC14.1, JP118.1, SJ56.1
~IRQ14: IC15.1, JP127.1, SJ60.1
~IRQ15: IC16.1, JP136.1, SJ64.1
~IRQ16: IC17.1, JP145.1, SJ68.1
~IRQ17: IC18.1, JP154.1, SJ72.1
~IRQ18: IC19.1, JP163.1, SJ76.1
~IRQ19: IC20.1, JP172.1, SJ80.1
~IRQ20: IC21.1, JP181.1, SJ84.1
~IRQ21: IC22.1, JP190.1, SJ88.1
~IRQ22: IC23.1, JP199.1, SJ92.1
~IRQ23: IC24.1, JP208.1, SJ96.1
~IRQ24: IC25.1, JP217.1, SJ100.1
~IRQ25: IC26.1, JP226.1, SJ104.1
~IRQ26: IC27.1, JP235.1, SJ108.1
~IRQ27: IC28.1, JP244.1, SJ112.1
~IRQ28: IC29.1, JP253.1, SJ116.1
~IRQ29: IC30.1, JP262.1, SJ120.1
~IRQ30: IC31.1, JP271.1, SJ124.1
~IRQ31: IC32.1, JP280.1, SJ128.1
~IRQ32: IC33.1, JP289.1, SJ132.1
~IRQ33: IC34.1, JP298.1, SJ136.1
~IRQ34: IC35.1, JP307.1, SJ140.1
~IRQ35: IC36.1, JP316.1, SJ144.1
~IRQ36: IC37.1, JP325.1, SJ148.1
~IRQ37: IC38.1, JP334.1, SJ152.1
~IRQ38: IC39.1, JP343.1, SJ156.1
~IRQ39: IC40.1, JP352.1, SJ160.1
~IRQ40: IC41.1, JP361.1, SJ164.1
~IRQ41: IC42.1, JP370.1, SJ168.1
~IRQ42: IC43.1, JP379.1, SJ172.1
~IRQ43: IC44.1, JP388.1, SJ176.1
~IRQ44: IC45.1, JP397.1, SJ180.1
~IRQ45: IC46.1, JP406.1, SJ184.1
~IRQ46: IC47.1, JP415.1, SJ188.1
~IRQ47: IC48.1, JP424.1, SJ192.1
~IRQ_PU: R4.1, SJ4.2
~IRQ_PU1: R8.1, SJ8.2
~IRQ_PU2: R12.1, SJ12.2
~IRQ_PU3: R16.1, SJ16.2
~IRQ_PU4: R20.1, SJ20.2
~IRQ_PU5: R24.1, SJ24.2
~IRQ_PU6: R28.1, SJ28.2
~IRQ_PU7: R32.1, SJ32.2
~IRQ_PU8: R36.1, SJ36.2
~IRQ_PU9: R40.1, SJ40.2
~IRQ_PU10: R44.1, SJ44.2
~IRQ_PU11: R48.1, SJ48.2
~IRQ_PU12: R52.1, SJ52.2
~IRQ_PU13: R56.1, SJ56.2
~IRQ_PU14: R60.1, SJ60.2
~IRQ_PU15: R64.1, SJ64.2
~IRQ_PU16: R68.1, SJ68.2
~IRQ_PU17: R72.1, SJ72.2
~IRQ_PU18: R76.1, SJ76.2
~IRQ_PU19: R80.1, SJ80.2
~IRQ_PU20: R84.1, SJ84.2
~IRQ_PU21: R88.1, SJ88.2
~IRQ_PU22: R92.1, SJ92.2
~IRQ_PU23: R96.1, SJ96.2
~IRQ_PU24: R100.1, SJ100.2
~IRQ_PU25: R104.1, SJ104.2
~IRQ_PU26: R108.1, SJ108.2
~IRQ_PU27: R112.1, SJ112.2
~IRQ_PU28: R116.1, SJ116.2
~IRQ_PU29: R120.1, SJ120.2
~IRQ_PU30: R124.1, SJ124.2
~IRQ_PU31: R128.1, SJ128.2
~IRQ_PU32: R132.1, SJ132.2
~IRQ_PU33: R136.1, SJ136.2
~IRQ_PU34: R140.1, SJ140.2
~IRQ_PU35: R144.1, SJ144.2
~IRQ_PU36: R148.1, SJ148.2
~IRQ_PU37: R152.1, SJ152.2
~IRQ_PU38: R156.1, SJ156.2
~IRQ_PU39: R160.1, SJ160.2
~IRQ_PU40: R164.1, SJ164.2
~IRQ_PU41: R168.1, SJ168.2
~IRQ_PU42: R172.1, SJ172.2
~IRQ_PU43: R176.1, SJ176.2
~IRQ_PU44: R180.1, SJ180.2
~IRQ_PU45: R184.1, SJ184.2
~IRQ_PU46: R188.1, SJ188.2
~IRQ_PU47: R192.1, SJ192.2

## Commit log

2013-08-09 Adding board files, code and README
2013-12-05 Adding Bildr Arduino sketch
2015-08-11 created giant panel v13
2015-08-19 test
